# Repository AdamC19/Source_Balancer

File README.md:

# Source Balancer
The properly named source balancer. See [this page on my website](http://www.acordingley.us/load_balancer/) for more background.

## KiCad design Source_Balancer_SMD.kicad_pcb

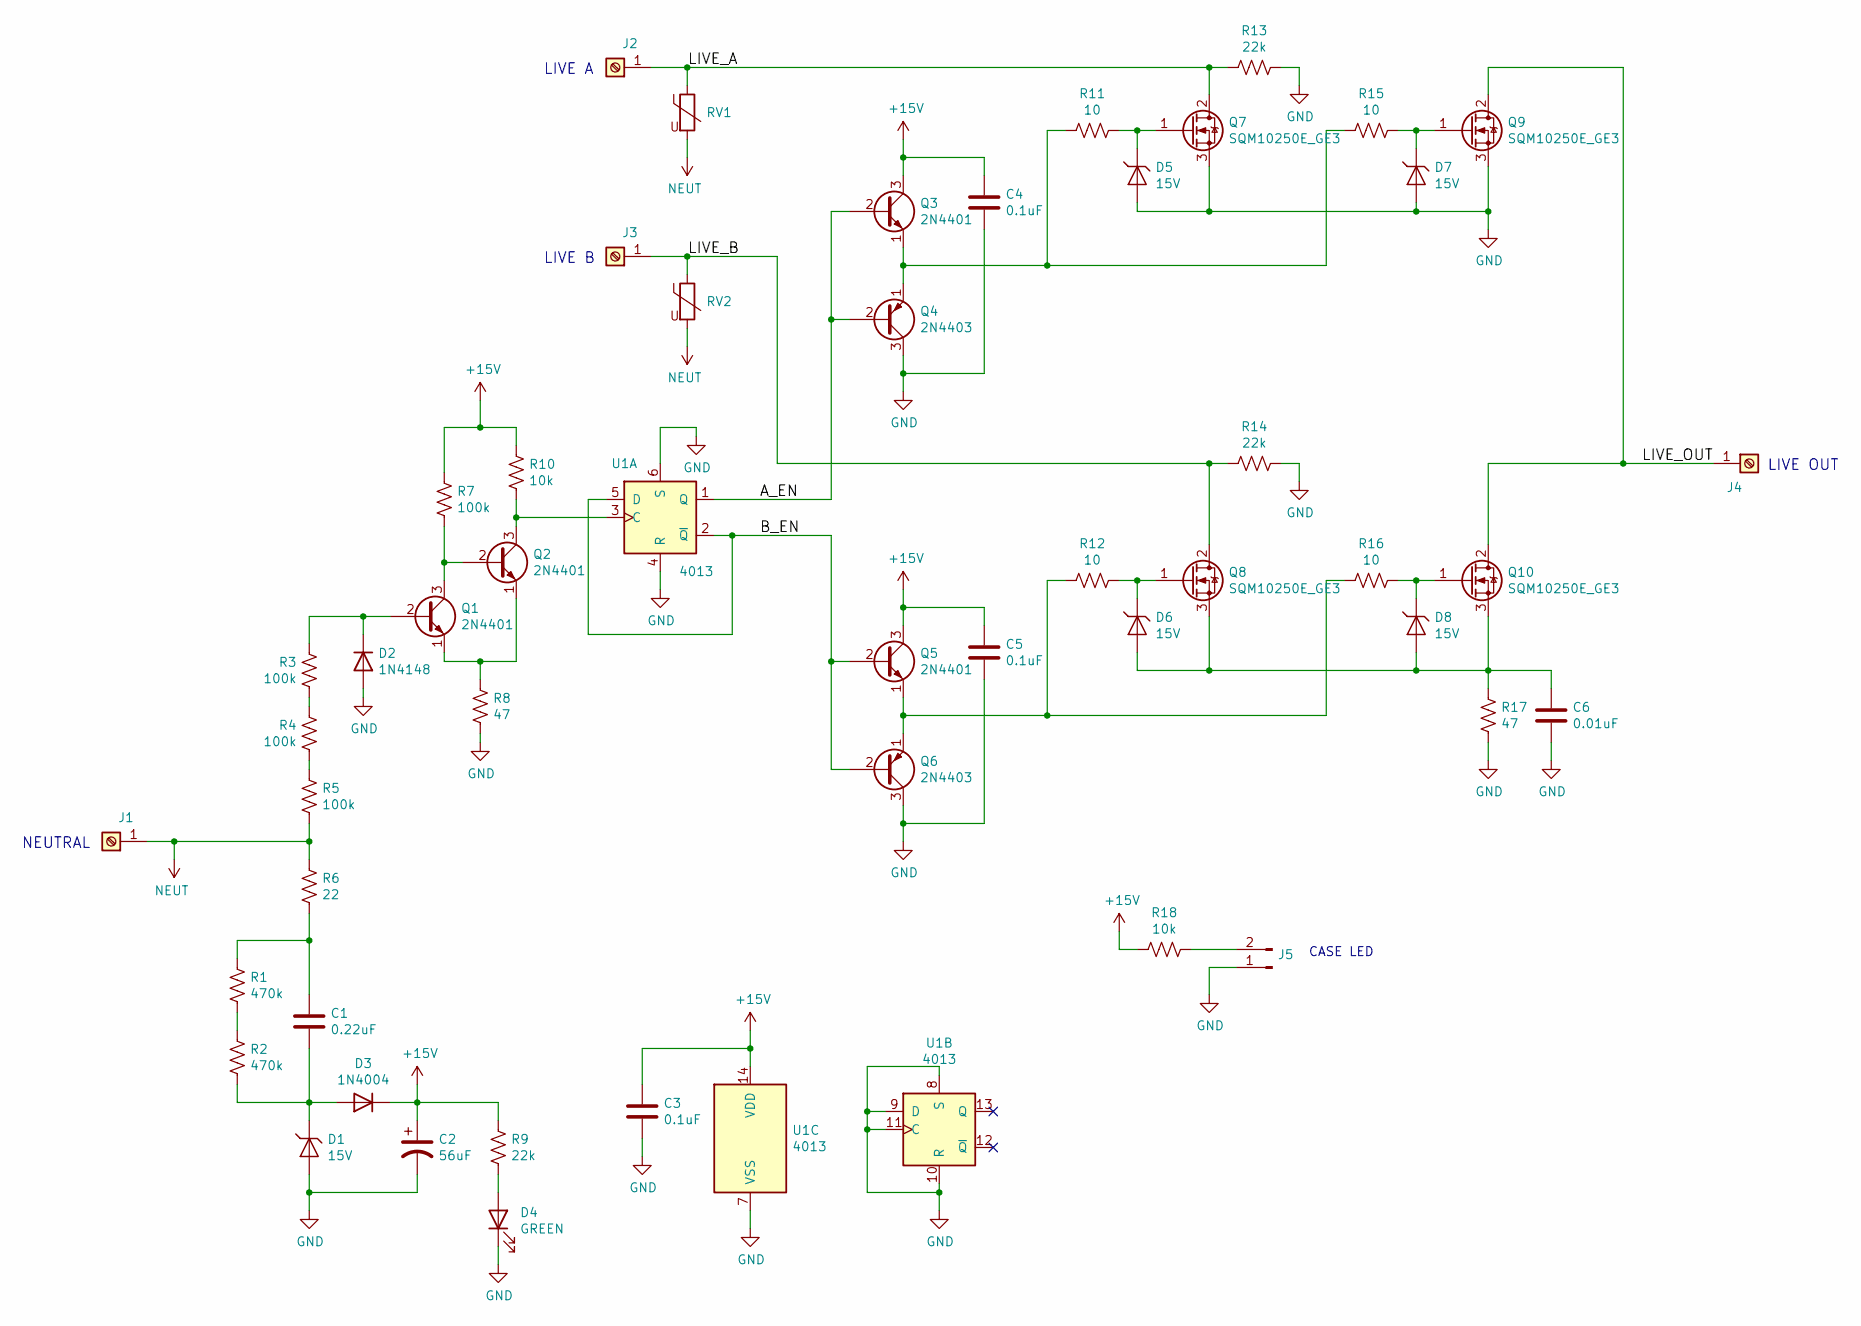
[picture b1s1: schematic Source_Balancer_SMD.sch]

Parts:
C1: 0.22uF; C_Rect_L18.0mm_W8.0mm_P15.00mm_FKS3_FKP3; MFG_PN R463I322000M2M
C2: 56uF; CP_Elec_8x10
C3, C4, C5: 0.1uF; C_0603_1608Metric
C6: 0.01uF; C_0603_1608Metric
D1: 15V; D_SMA
D2: 1N4148; D_SOD-123
D3: 1N4004; D_SOD-123
D4: GREEN; LED_0805_2012Metric; MFG_PN APT2012LZGCK
D5, D6, D7, D8: 15V; D_SOD-123
J1, J2, J3, J4: Screw_Terminal_01x01; MountingHole_5.3mm_M5_Pad_Via
J5: Conn_01x02_Male; JST_XH_B2B-XH-A_1x02_P2.50mm_Vertical
Q1, Q2, Q3, Q5: 2N4401; SOT-23
Q4, Q6: 2N4403; SOT-23
Q7, Q8, Q9, Q10: SQM10250E_GE3; TO-263-2-HV
R1, R2: 470k; R_1206_3216Metric
R3, R4, R5: 100k; R_1206_3216Metric
R6: 22; R_Axial_DIN0414_L11.9mm_D4.5mm_P15.24mm_Horizontal
R7: 100k; R_0805_2012Metric
R8, R17: 47; R_0805_2012Metric
R9: 22k; R_0805_2012Metric
R10, R18: 10k; R_0805_2012Metric
R11, R12, R15, R16: 10; R_0805_2012Metric
R13, R14: 22k; R_1206_3216Metric
RV1, RV2: Varistor; RV_Disc_D12mm_W4.5mm_P7.5mm
U1: 4013; SOIC-14_3.9x8.7mm_P1.27mm

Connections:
+15V: C2.1, C3.1, C4.1, C5.1, D3.1 (K), Q3.3 (C), Q5.3 (C), R7.2, R9.2, R10.2, R18.2, U1.14 (VDD)
/A_EN: Q3.2 (B), Q4.2 (B), U1.1 (Q)
/B_EN: Q5.2 (B), Q6.2 (B), U1.2 (~Q), U1.5 (D)
/LIVE_A: J2.1, Q7.2 (D), R13.2, RV1.1
/LIVE_B: J3.1, Q8.2 (D), R14.2, RV2.1
/LIVE_OUT: J4.1, Q9.2 (D), Q10.2 (D)
GND: C2.2, C3.2, C4.2, C5.2, C6.2, D1.2 (A), D2.2 (A), D4.1 (K), D5.2 (A), D7.2 (A), J5.1, Q4.3 (C), Q6.3 (C), Q7.3 (S), Q9.3 (S), R8.2, R13.1, R14.1, R17.1, U1.4 (R), U1.6 (S), U1.7 (VSS), U1.8 (S), U1.9 (D), U1.10 (R), U1.11 (C)
NEUT: J1.1, R5.1, R6.2, RV1.2, RV2.2
unnamed: C1.1, R1.1, R6.1
unnamed: C1.2, D1.1 (K), D3.2 (A), R2.2
unnamed: C6.1, D6.2 (A), D8.2 (A), Q8.3 (S), Q10.3 (S), R17.2
unnamed: D2.1 (K), Q1.2 (B), R3.2
unnamed: D4.2 (A), R9.1
unnamed: D5.1 (K), Q7.1 (G), R11.1
unnamed: D6.1 (K), Q8.1 (G), R12.1
unnamed: D7.1 (K), Q9.1 (G), R15.1
unnamed: D8.1 (K), Q10.1 (G), R16.1
unnamed: J5.2, R18.1
unnamed: Q1.1 (E), Q2.1 (E), R8.1
unnamed: Q1.3 (C), Q2.2 (B), R7.1
unnamed: Q2.3 (C), R10.1, U1.3 (C)
unnamed: Q3.1 (E), Q4.1 (E), R11.2, R15.2
unnamed: Q5.1 (E), Q6.1 (E), R12.2, R16.2
unnamed: R1.2, R2.1
unnamed: R3.1, R4.2
unnamed: R4.1, R5.2

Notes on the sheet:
NEUTRAL
LIVE B
LIVE A
LIVE OUT
CASE LED

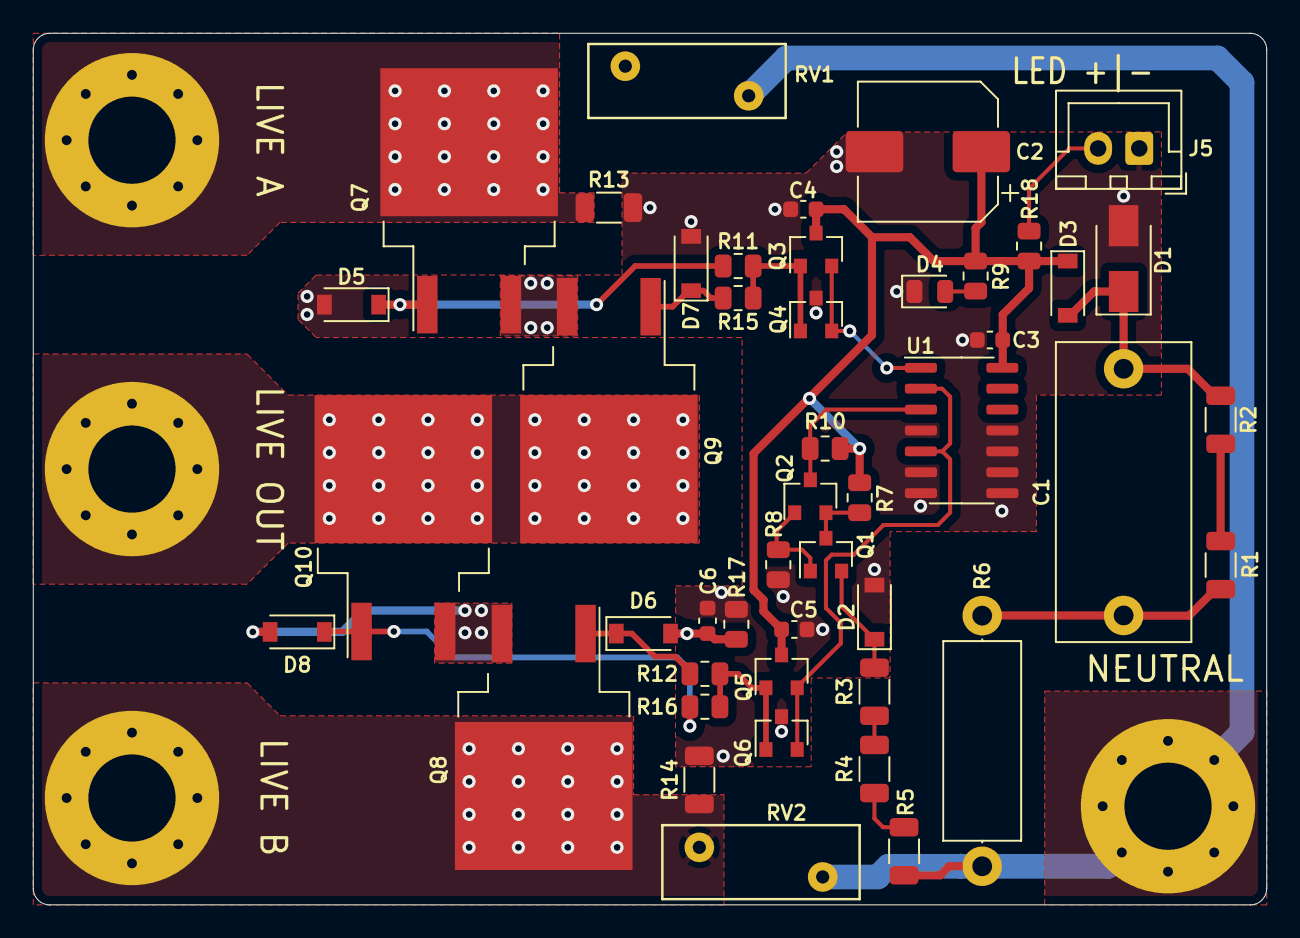
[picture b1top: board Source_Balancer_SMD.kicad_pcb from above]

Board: 2 copper layers, 75.0 x 53.0 mm, 50 parts (0 on the bottom side), 26 nets.

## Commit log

2021-12-18 Add pdf of schematic and rendering of board
2022-01-03 BJTs are messed up

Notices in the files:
Source_Balancer_SMD.kicad_pcb:
(C) 2021 ADAM CORDINGLEY
